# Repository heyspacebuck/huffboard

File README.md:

# Huffboard

## A board for the Huffbox

# [Learn about the Huffbox HERE!](https://huffbox.aliencat.dev/)

This is a first attempt at improving the connections between the control device--a Raspberry Pi 4--and peripherals using the Pi's GPIO (electromagnets, fans, lights, LED matrix). It was designed to be easy to assemble using JLCPCB's assembly service. If you want to order a board through JLC's assembly service, you will need the files found in the `jlcpcb/production_files` directory.

## Software necessary to inspect the design files

- [KiCad 8](https://www.kicad.org/) or a later version compatible with KiCad 8 projects
- To look at the JLCPCB assembly parts used, it helps to have the [KiCad JLCPCB Tools plugin by Bouni](https://github.com/bouni/kicad-jlcpcb-tools)

## Known issues

- Power has to be supplied to the Pi using its regular power cable. I had hoped to power it through the Huffboard, but the Raspberry Pi Foundation's [guidelines on powering a Pi via a hat](https://github.com/raspberrypi/hats/blob/bcc5afd013360c93f258c9e2cd7d7131e5ca659f/backpowering-diagram.png) are literally sketchy, and their recommended parts don't provide enough power to keep the Pi on.
- I don't like how the relays work or the 0Ω resistors being used as configuration pins. Going to change that in the next revision.

## Schematic

[A PDF of the schematic can be found here.](Schematic.pdf)

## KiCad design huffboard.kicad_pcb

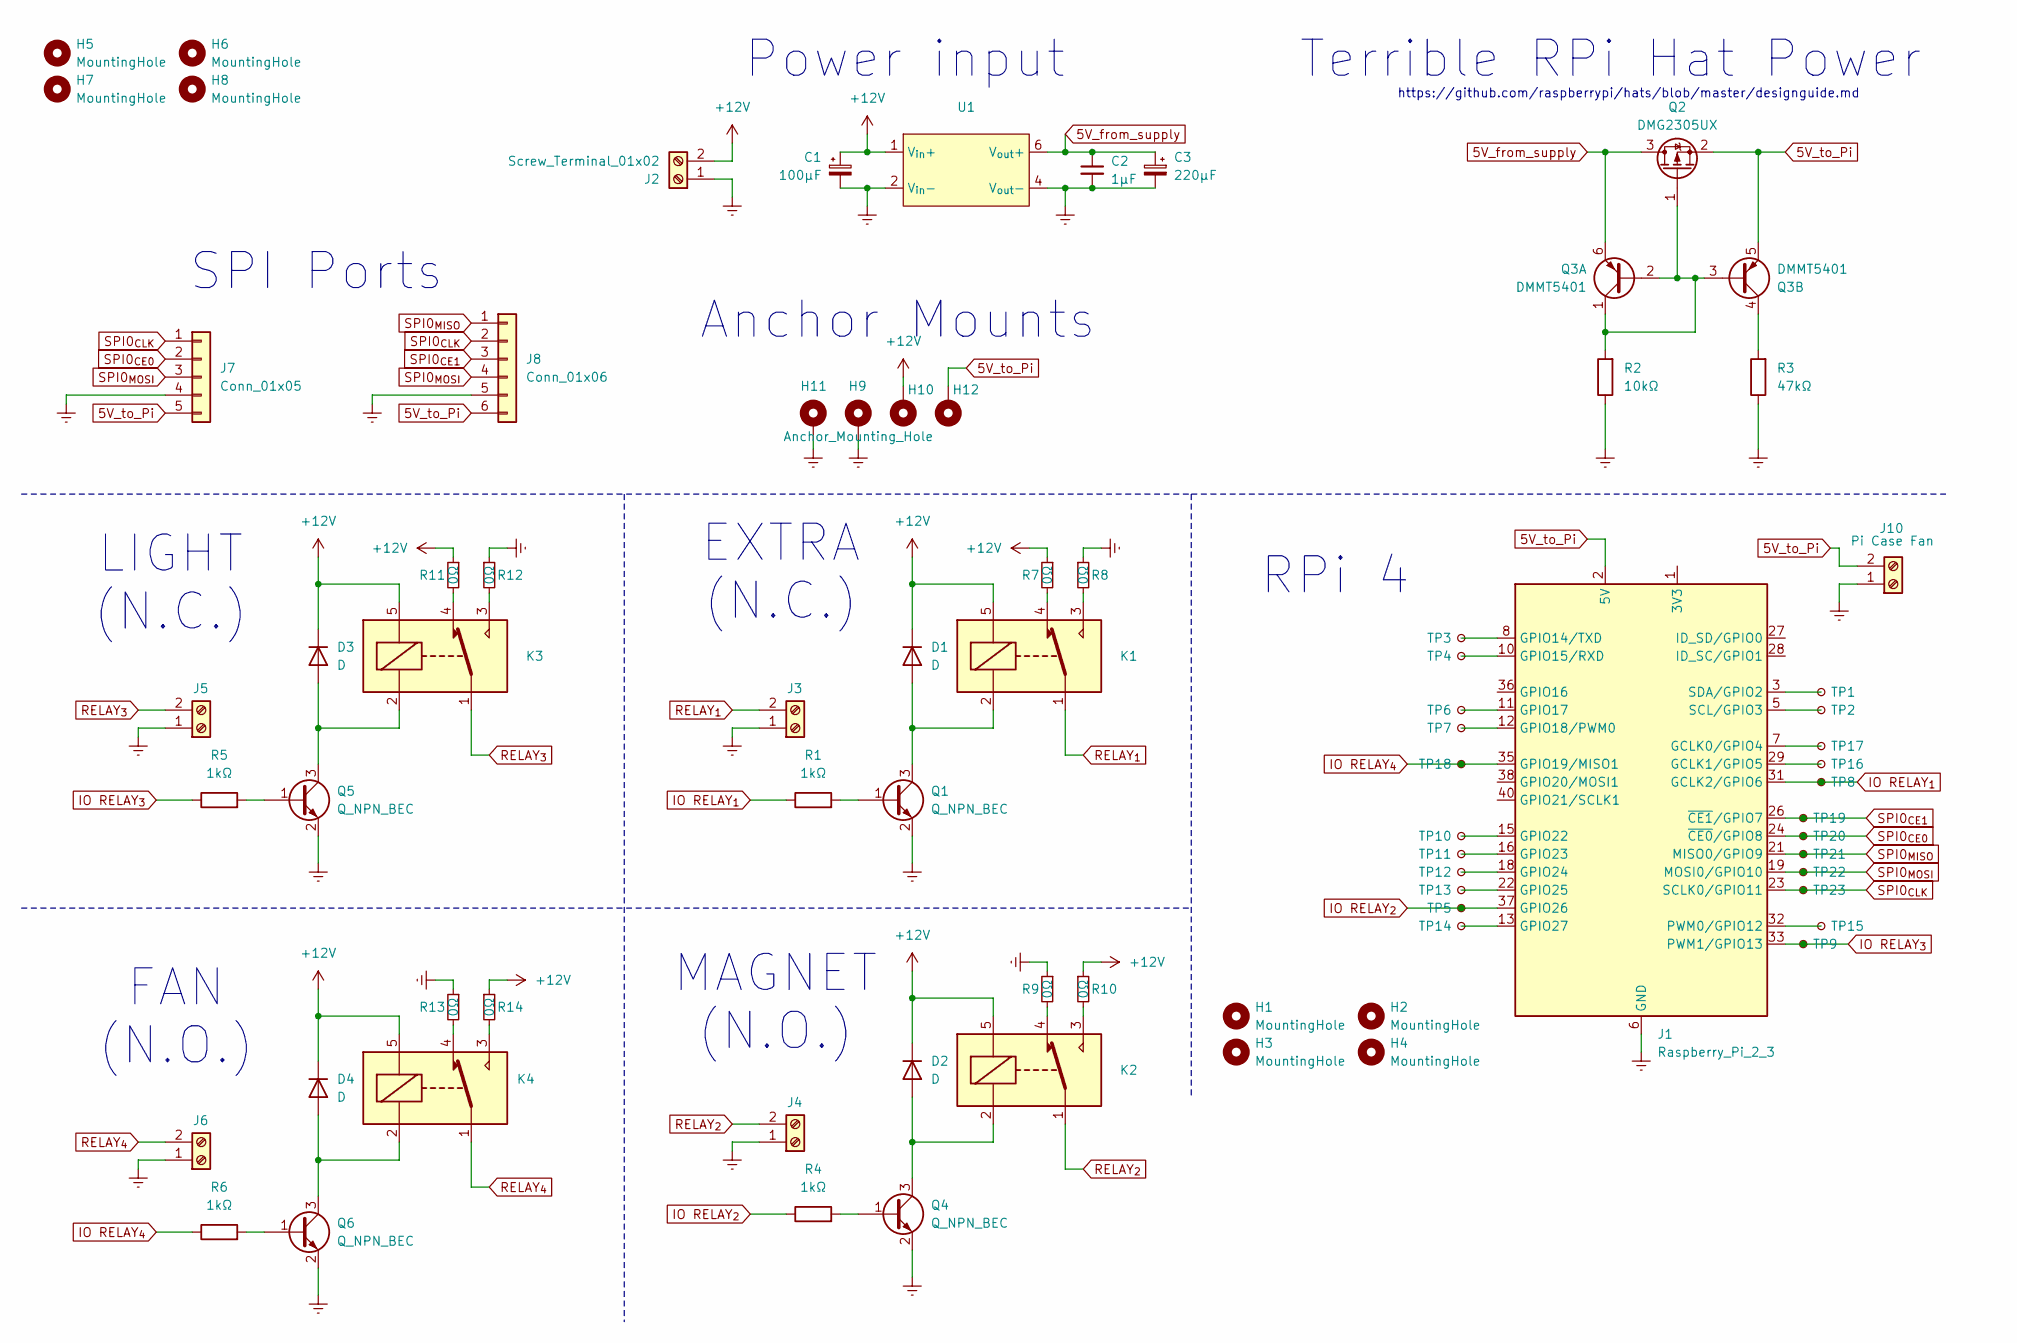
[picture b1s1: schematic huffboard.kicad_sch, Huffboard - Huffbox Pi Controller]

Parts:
C1: 100μF; CP_Elec_6.3x7.7
C2: 1μF; C_0603_1608Metric
C3: 220μF; CP_Elec_6.3x7.7
D1, D2, D3, D4: D; D_SOD-123F
H1, H2, H3, H4: MountingHole; SMTSO2545CTJ
H5, H6, H7, H8: MountingHole; MountingHole_3.2mm_M3
H9, H10, H11, H12: Anchor_Mounting_Hole; MountingHole_3.2mm_M3_Pad_Via
J1: Raspberry_Pi_2_3; IDC-Header_2x20_P2.54mm_Vertical
J2: Screw_Terminal_01x02; Terminal_Screw_7.62
J3, J4, J5, J6: Screw_Terminal_01x02; TerminalBlock_Phoenix_MKDS-1,5-2-5.08_1x02_P5.08mm_Horizont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
J7: Conn_01x05; JST_PH_B5B-PH-K_1x05_P2.00mm_Vertical
J8: Conn_01x06; JST_PH_B6B-PH-K_1x06_P2.00mm_Vertical
J10: Pi Case Fan; PinSocket_1x02_P2.54mm_Vertical
K1, K2, K3, K4: SANYOU_SRD_Form_C; Relay_SPDT_SANYOU_SRD_Series_Form_C
Q1, Q4, Q5, Q6: Q_NPN_BEC; SOT-23
Q2: DMG2305UX; SOT-23
Q3: DMMT5401; SOT-23-6
R1, R4, R5, R6: 1kΩ; R_0603_1608Metric
R2: 10kΩ; R_0603_1608Metric
R3: 47kΩ; R_0603_1608Metric
R7, R8, R9, R10, R11, R12, R13, R14: 0Ω; R_1206_3216Metric
TP1, TP2, TP3, TP4, TP5, TP6, TP7, TP8, TP9, TP10, TP11, TP12, TP13, TP14, TP15, TP16, TP17, TP18, TP19, TP20, TP21, TP22, TP23: TestPoint_Small; simple_testpoint_pinout
U1: TDK15-XXSXX-MODULE

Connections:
5V_from_supply: C2.1, C3.1, Q2.3 (D), Q3.6 (E1), U1.6 (V_{out}+)
5V_to_Pi: H12.1, J1.2 (5V), J1.4 (5V), J7.5, J8.6, J10.2, Q2.2 (S), Q3.5 (E2)
+12V: C1.1, D1.1 (K), D2.1 (K), D3.1 (K), D4.1 (K), H10.1, J2.2, K1.5, K2.5, K3.5, K4.5, R7.1, R10.1, R11.1, R14.1, U1.1 (V_{in}+)
GNDREF: C1.2, C2.2, C3.2, H9.1, H11.1, J1.6 (GND), J1.9 (GND), J1.14 (GND), J1.20 (GND), J1.25 (GND), J1.30 (GND), J1.34 (GND), J1.39 (GND), J2.1, J3.1, J4.1, J5.1, J6.1, J7.4, J8.5, J10.1, Q1.2 (E), Q4.2 (E), Q5.2 (E), Q6.2 (E), R2.1, R3.1, R8.1, R9.1, R12.1, R13.1, U1.2 (V_{in}-), U1.4 (V_{out}-)
IO RELAY_{1}: J1.31 (GCLK2/GPIO6), R1.1, TP8.1
IO RELAY_{2}: J1.37 (GPIO26), R4.1, TP5.1
IO RELAY_{3}: J1.33 (PWM1/GPIO13), R5.1, TP9.1
IO RELAY_{4}: J1.35 (GPIO19/MISO1), R6.1, TP18.1
unnamed: D1.2 (A), K1.2, Q1.3 (C)
unnamed: D2.2 (A), K2.2, Q4.3 (C)
unnamed: D3.2 (A), K3.2, Q5.3 (C)
unnamed: D4.2 (A), K4.2, Q6.3 (C)
unnamed: J1.1 (3V3), J1.17 (3V3)
unnamed: J1.7 (GCLK0/GPIO4), TP17.1
unnamed: J1.29 (GCLK1/GPIO5), TP16.1
unnamed: J1.8 (GPIO14/TXD), TP3.1
unnamed: J1.10 (GPIO15/RXD), TP4.1
unnamed: J1.11 (GPIO17), TP6.1
unnamed: J1.12 (GPIO18/PWM0), TP7.1
unnamed: J1.15 (GPIO22), TP10.1
unnamed: J1.16 (GPIO23), TP11.1
unnamed: J1.18 (GPIO24), TP12.1
unnamed: J1.22 (GPIO25), TP13.1
unnamed: J1.13 (GPIO27), TP14.1
unnamed: J1.32 (PWM0/GPIO12), TP15.1
unnamed: J1.5 (SCL/GPIO3), TP2.1
unnamed: J1.3 (SDA/GPIO2), TP1.1
unnamed: K1.3, R8.2
unnamed: K1.4, R7.2
unnamed: K2.3, R10.2
unnamed: K2.4, R9.2
unnamed: K3.3, R12.2
unnamed: K3.4, R11.2
unnamed: K4.3, R14.2
unnamed: K4.4, R13.2
unnamed: Q1.1 (B), R1.2
unnamed: Q2.1 (G), Q3.1 (C1), Q3.2 (B1), Q3.3 (B2), R2.2
unnamed: Q3.4 (C2), R3.2
unnamed: Q4.1 (B), R4.2
unnamed: Q5.1 (B), R5.2
unnamed: Q6.1 (B), R6.2
RELAY_{1}: J3.2, K1.1
RELAY_{2}: J4.2, K2.1
RELAY_{3}: J5.2, K3.1
RELAY_{4}: J6.2, K4.1
SPI0_{CE0}: J1.24 (~CE0/GPIO8), J7.2, TP20.1
SPI0_{CE1}: J1.26 (~CE1/GPIO7), J8.3, TP19.1
SPI0_{CLK}: J1.23 (SCLK0/GPIO11), J7.1, J8.2, TP23.1
SPI0_{MISO}: J1.21 (MISO0/GPIO9), J8.1, TP21.1
SPI0_{MOSI}: J1.19 (MOSI0/GPIO10), J7.3, J8.4, TP22.1

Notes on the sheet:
SPI Ports
MAGNET (N.O.)
Anchor Mounts
RPi 4
Terrible RPi Hat Power
FAN (N.O.)
EXTRA (N.C.)
Power input
https://github.com/raspberrypi/hats/blob/master/designguide.md
LIGHT (N.C.)

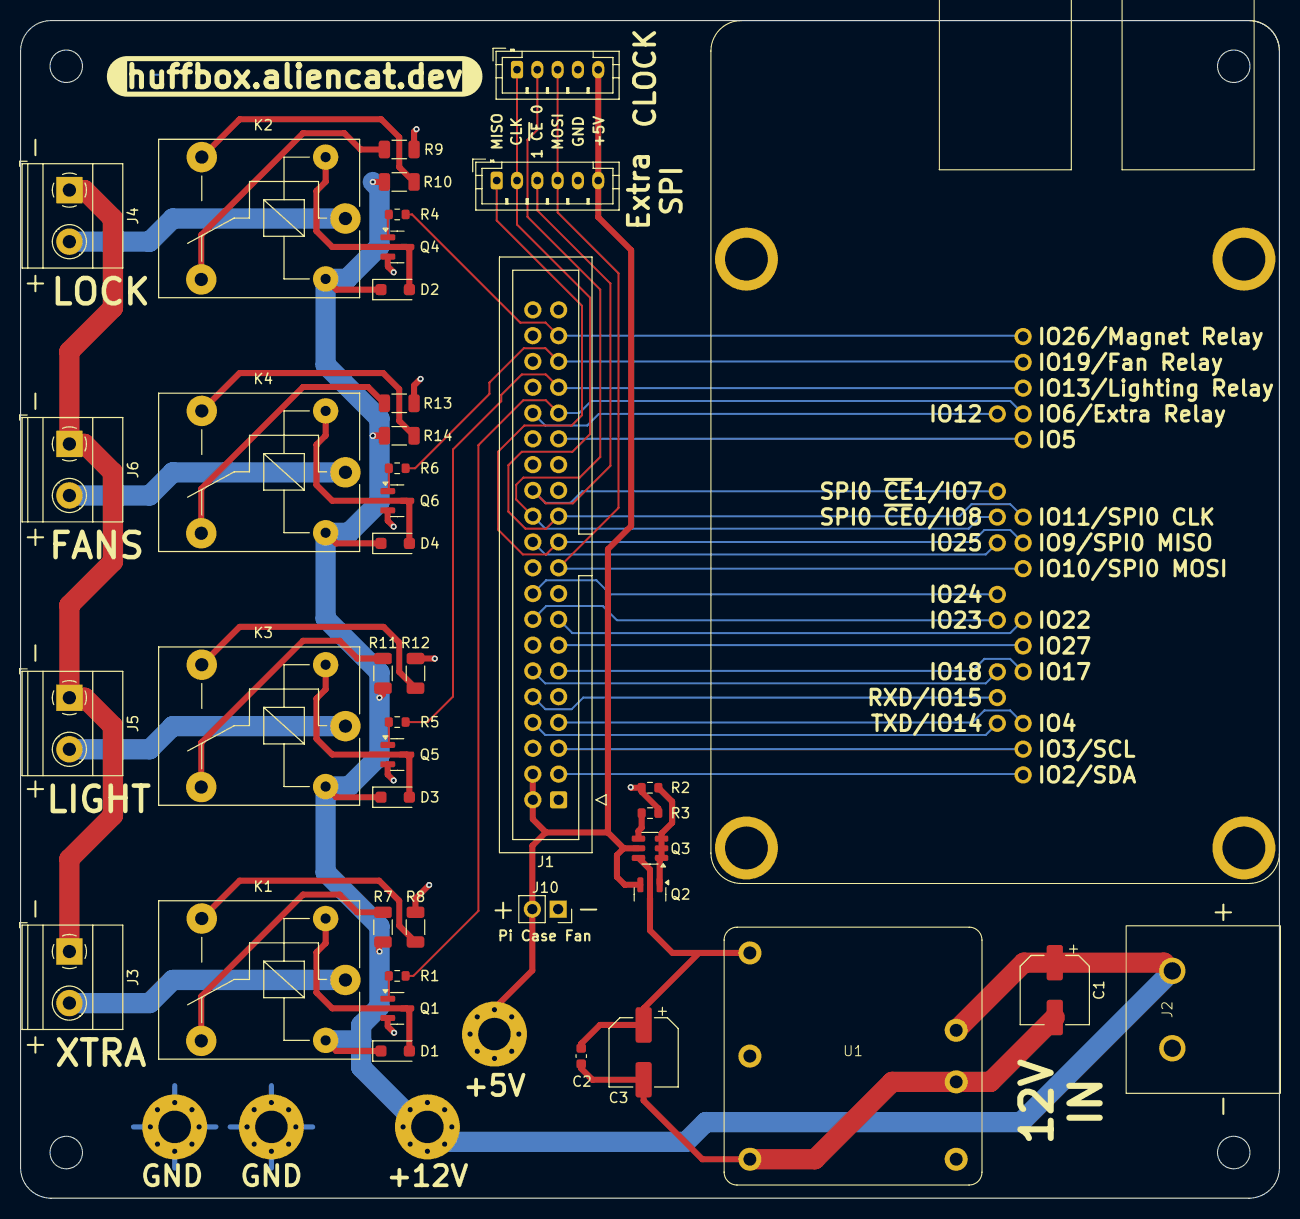
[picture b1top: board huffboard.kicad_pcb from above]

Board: 2 copper layers, 124.0 x 116.0 mm, 76 parts (0 on the bottom side), 50 nets.

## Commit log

2024-05-14 init commit

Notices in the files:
huffboard.kicad_pcb:
CC BY-NC-SA 4.0
